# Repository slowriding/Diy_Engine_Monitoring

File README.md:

# Diy_Engine_Monitoring
Read and display Powertrain sensors and control outputs with DIY PCB, code and display.

Project started to facilitate features lost due to swapping in newer engine into older computer controlled vehicle.  
It overlays a secondary set of sensors and a display unit showing gauges.  The controller drives outputs for variable speed loads like fans and fuel pump and switched loads.
Goals are for the system to be as simple as possible, hackable and start immediately without having to boot an operating system.

Current design uses a common Arduino module programmed in C.  This project welcomes submissions of improvements or complete redesigns.
OBDII and GM LAN integration are intended but not completed.

Test article implementation:
2002 Chevrolet Tahoe with original 5.3L, LS3 GEN III, gas engine that failed and Chevrolet Performance E-ROD LS3, LS3 GEN IV, powertrain was installed with 6-speed manual transmission necessitating ECU swap.  The communications network is too different to interconnect directly.  The original dashboard gauges and A/C became completely non-functional due to removed original ECU and features not implemented in newer but generic engine controller.

This project side steps difficulties in attempting to build a protocol converter; for the time being.  Requirements are met by adding a layer of sensors and outputs to replace missing features and adding some extra functionality.  I (original contributor) intend to hack my 2002 Tahoe dash adding pwm driver outputs to drive stock gauge needles.  This will also control new style variable volume A/C compressor based on pressure and temperature sensors. 

Design overview:
Sensors types:  // currently implemented but not all yet working
	Resistive (coolant & oil temp and fuel level).
	0-5V transducers (oil, fuel, evap. and A/C high pressure)
	0-5V ECU outputs (throttle and map)
	Pulse frequency (RPM and vehicle speed)
	Switched (ac & recirculation requests)
	1-wire temperature probes (outside air and A/C condenser temperatures)
 
Outputs types:
	PWM Gauges Drivers (fuel level, oil pressure, coolant temperature, MPH)
	PWM Loads (fan1, fan2, Variable A/C compressor, Fuel Pump speed)

Interface:
	Display - Nextion brand Intelligent LCD display used due to it’s simple serial port/text based connection.  
 	All the graphics are stored and processed on the display. 
	I2c & SPI connections for future ODB2 interfaces.
Programming:
	Currently written in C, with migration to RUST intended for future releases.
	The Tahoe.h file isolates MCU pin definitions, calibrations and variable definitions.

Please consider contributing to this evolving project as much can be improved

Files: 
	Schmatic: See .pdf files in root or Open directorys in KiCAD One is the PCB and the other shows the wiring currenly used on authors Tahoe
 	Code: Open Using Arduino software 
  	PCB design files are newer than revision being tested (PCB photo).  Newer version has better voltage regulation and is physiclly smaller.

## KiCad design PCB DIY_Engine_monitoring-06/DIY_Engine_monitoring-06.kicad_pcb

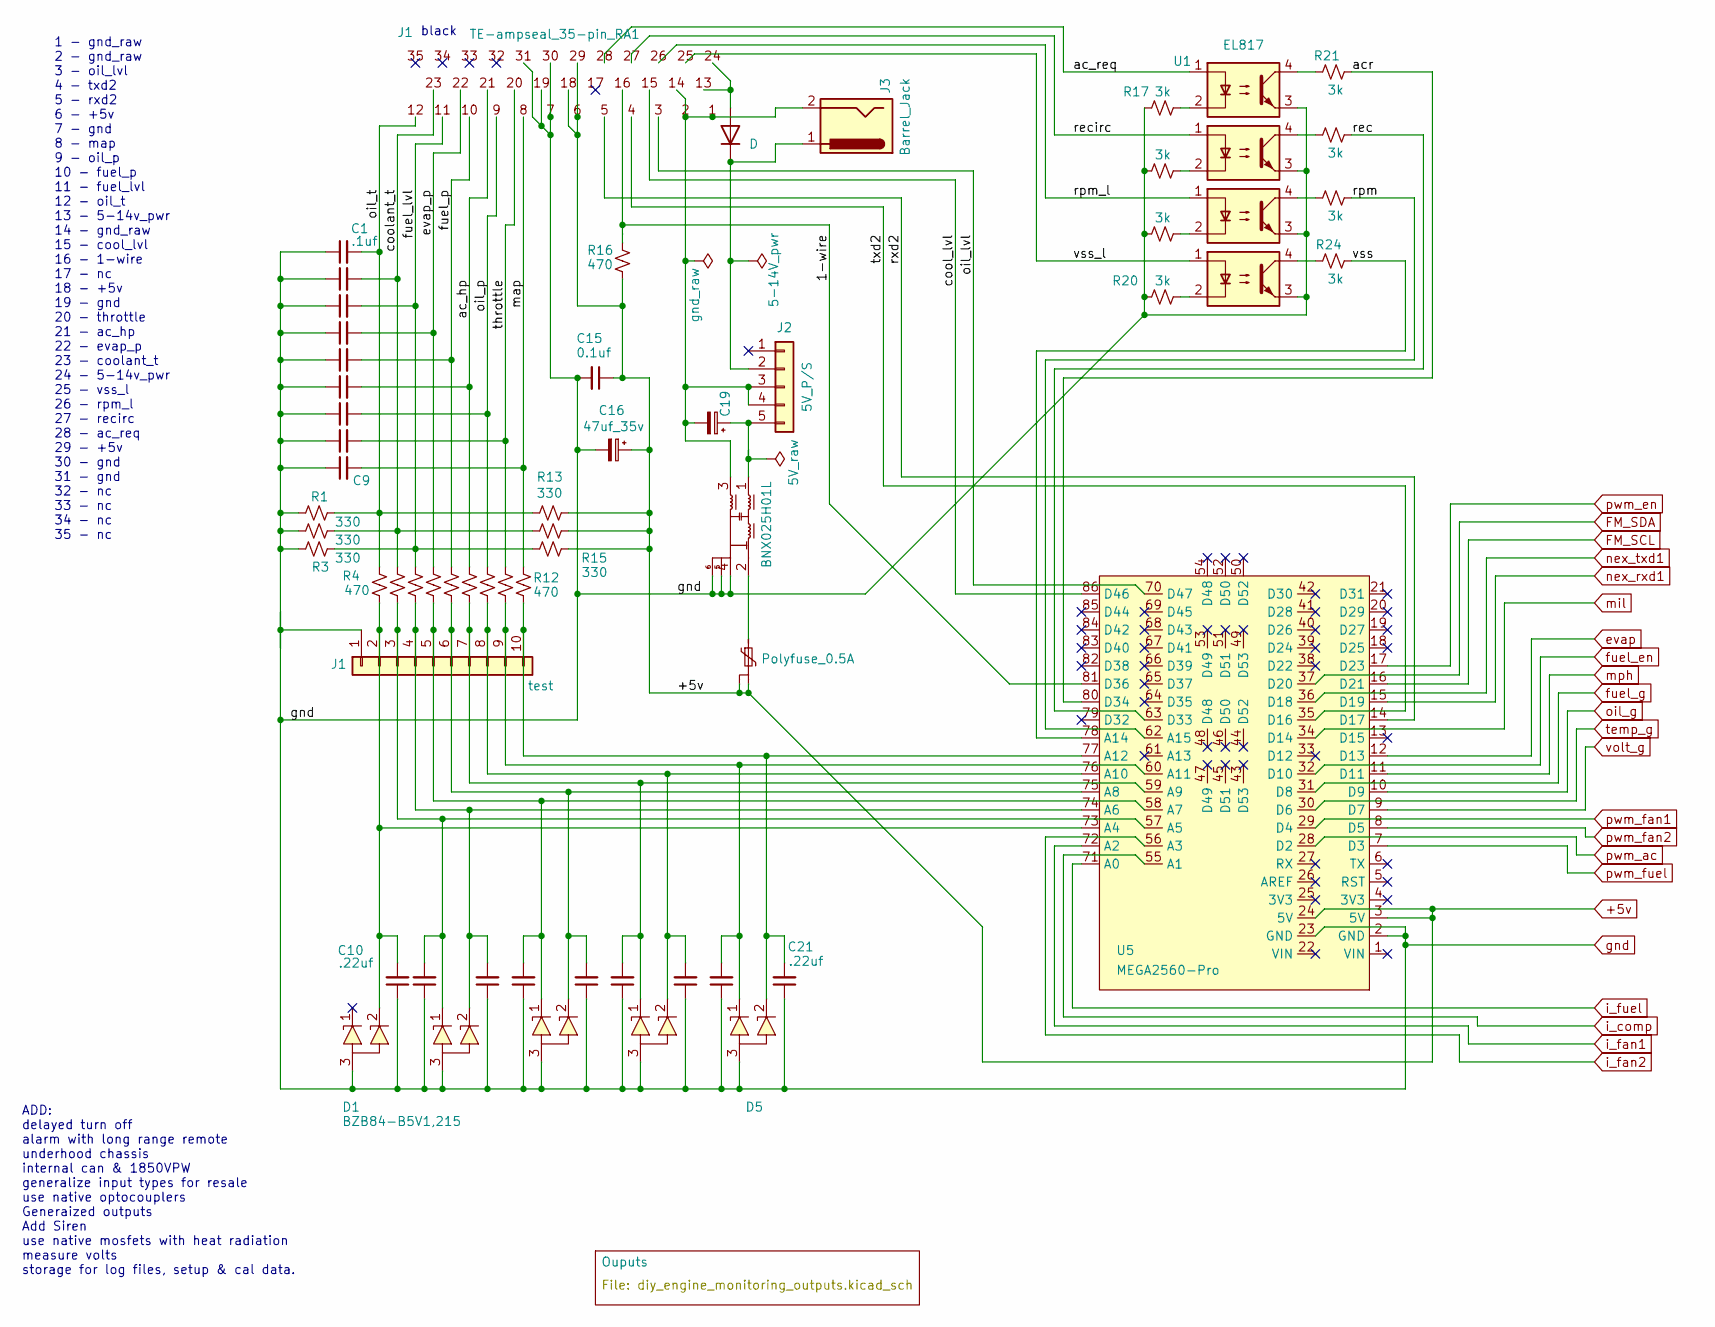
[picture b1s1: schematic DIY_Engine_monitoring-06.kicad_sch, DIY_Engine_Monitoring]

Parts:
C1, C2, C3, C4, C5, C6, C7, C8, C9: .1uf; C_0805_2012Metric
C10, C11, C12, C13, C14, C17, C18, C20, C21: .22uf; C_0805_2012Metric
C15: 0.1uf; C_0805_2012Metric
C16: 47uf_35v; CP_Radial_D6.3mm_P2.50mm
C19: 47uf_50v; CP_Radial_D8.0mm_P5.00mm
D1, D2, D3, D4, D5: BZB84-B5V1,215; SOT-23
D22: D
F1: Polyfuse_0.5A; Littelfuse_PolyZen-LS
FL1: BNX025H01L; Filter_Murata_BNX025_ThermalVias
J1: test; PinHeader_1x10_P2.54mm_Vertical
J2: 5V_P/S; PinSocket_1x05_P2.54mm_Vertical
J3: Barrel_Jack; BarrelJack_Horizontal
R1, R2, R3, R13, R14, R15: 330; R_0805_2012Metric_Pad1.20x1.40mm_HandSolder
R4, R5, R6, R7, R8, R9, R10, R11, R12, R16: 470; R_0805_2012Metric_Pad1.20x1.40mm_HandSolder
R17, R18, R19, R20, R21, R22, R23, R24: 3k; R_0805_2012Metric
TE-ampseal_35-pin_RA1: J1; TE_AMPSEAL_1-776163-x_3Rows_35_P0.4mm_Horizontal
U1, U2, U3, U4: EL817; DIP-4_W7.62mm
U5: MEGA2560-Pro

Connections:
+5v: C15.1, C16.1, F1.2, F1.3, R13.1, R14.1, R15.2, R16.2, TE-ampseal_35-pin_RA1.6, TE-ampseal_35-pin_RA1.18, TE-ampseal_35-pin_RA1.29, U5.3 (5V), U5.24 (5V); also elsewhere on the board
/1-wire: R16.1, TE-ampseal_35-pin_RA1.16, U5.81 (D36)
/ac_hp: C6.2, R9.1, TE-ampseal_35-pin_RA1.21
/ac_req: TE-ampseal_35-pin_RA1.28, U1.1
/acr: R21.2, U5.80 (D34)
/cool_lvl: TE-ampseal_35-pin_RA1.15, U5.86 (D46)
/coolant_t: C2.2, R2.2, R5.2, R14.2, TE-ampseal_35-pin_RA1.23
/evap_p: C4.2, R7.1, TE-ampseal_35-pin_RA1.22
/fuel_lvl: C3.2, R3.2, R6.1, R15.1, TE-ampseal_35-pin_RA1.11
/fuel_p: C5.2, R8.1, TE-ampseal_35-pin_RA1.10
/map: C9.2, R12.1, TE-ampseal_35-pin_RA1.8
/oil_lvl: TE-ampseal_35-pin_RA1.3, U5.70 (D47)
/oil_p: C7.2, R10.1, TE-ampseal_35-pin_RA1.9
/oil_t: C1.2, R1.2, R4.1, R13.2, TE-ampseal_35-pin_RA1.12
/rec: R22.2, U5.63 (D33)
/recirc: TE-ampseal_35-pin_RA1.27, U2.1
/rpm: R23.2, U5.62 (A15)
/rpm_l: TE-ampseal_35-pin_RA1.26, U3.1
/rxd2: TE-ampseal_35-pin_RA1.5, U5.14 (D17)
/throttle: C8.2, R11.1, TE-ampseal_35-pin_RA1.20
/txd2: TE-ampseal_35-pin_RA1.4, U5.35 (D16)
/vss: R24.2, U5.78 (A14)
/vss_l: TE-ampseal_35-pin_RA1.25, U4.1
FM_SCL: U5.16 (D21); also elsewhere on the board
FM_SDA: U5.37 (D20); also elsewhere on the board
unnamed: C10.2, D1.2 (A), J1.2, R4.2, U5.73 (A4)
unnamed: C12.2, D2.2 (A), J1.4, R6.2, U5.74 (A6)
unnamed: C14.2, D3.2 (A), J1.6, R8.2, U5.75 (A8)
unnamed: C18.2, D4.2 (A), J1.8, R10.2, U5.76 (A10)
unnamed: C21.2, D5.2 (A), J1.10, R12.2, U5.77 (A12)
unnamed: F1.1, FL1.2
unnamed: C11.2, D2.1 (K), J1.3, R5.1, U5.57 (A5)
unnamed: C13.2, D3.1 (K), J1.5, R7.2, U5.58 (A7)
unnamed: C17.2, D4.1 (K), J1.7, R9.2, U5.59 (A9)
unnamed: C20.2, D5.1 (K), J1.9, R11.2, U5.60 (A11)
unnamed: C19.2, FL1.3, J2.3, J2.4, J3.2, TE-ampseal_35-pin_RA1.1, TE-ampseal_35-pin_RA1.2, TE-ampseal_35-pin_RA1.14
unnamed: C19.1, FL1.1, J2.5
unnamed: R17.2, U1.2
unnamed: R18.2, U2.2
unnamed: R19.2, U3.2
unnamed: R20.2, U4.2
unnamed: R21.1, U1.4
unnamed: R22.1, U2.4
unnamed: R23.1, U3.4
unnamed: R24.1, U4.4
evap: U5.12 (D13); also elsewhere on the board
fuel_en: U5.32 (D10); also elsewhere on the board
fuel_g: U5.31 (D8); also elsewhere on the board
gnd: C1.1, C2.1, C3.1, C4.1, C5.1, C6.1, C7.1, C8.1, C9.1, C10.1, C11.1, C12.1, C13.1, C14.1, C15.2, C16.2, C17.1, C18.1, C20.1, C21.1, D1.3 (K), D2.3 (K), D3.3 (K), D4.3 (K), D5.3 (K), FL1.4, FL1.5, FL1.6, J1.1, R1.1, R2.1, R3.1, R17.1, R18.1, R19.1, R20.1, TE-ampseal_35-pin_RA1.7, TE-ampseal_35-pin_RA1.19, TE-ampseal_35-pin_RA1.30, TE-ampseal_35-pin_RA1.31, U1.3, U2.3, U3.3, U4.3, U5.2 (GND), U5.23 (GND); also elsewhere on the board
i_comp: U5.55 (A1); also elsewhere on the board
i_fan1: U5.72 (A2); also elsewhere on the board
i_fan2: U5.56 (A3); also elsewhere on the board
i_fuel: U5.71 (A0); also elsewhere on the board
mil: U5.34 (D14); also elsewhere on the board
mph: U5.11 (D11); also elsewhere on the board
nex_rxd1: U5.15 (D19); also elsewhere on the board
nex_txd1: U5.36 (D18); also elsewhere on the board
oil_g: U5.10 (D9); also elsewhere on the board
pwm_ac: U5.28 (D2); also elsewhere on the board
pwm_en: U5.17 (D23); also elsewhere on the board
pwm_fan1: U5.29 (D4); also elsewhere on the board
pwm_fan2: U5.8 (D5); also elsewhere on the board
pwm_fuel: U5.7 (D3); also elsewhere on the board
temp_g: U5.30 (D6); also elsewhere on the board
volt_g: U5.9 (D7); also elsewhere on the board

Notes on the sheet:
ADD: delayed turn off alarm with long range remote underhood chassis internal can & 1850VPW generalize input types for resale use native optocouplers Generaized outputs Add Siren use native mosfets with heat radiation measure volts storage for log files, setup & cal data.
1 - gnd_raw 2 - gnd_raw 3 - oil_lvl 4 - txd2 5 - rxd2 6 - +5v 7 - gnd 8 - map 9 - oil_p 10 - fuel_p 11 - fuel_lvl 12 - oil_t 13 - 5-14v_pwr 14 - gnd_raw 15 - cool_lvl 16 - 1-wire 17 - nc 18 - +5v 19 - gnd 20 - throttle 21 - ac_hp 22 - evap_p 23 - coolant_t 24 - 5-14v_pwr 25 - vss_l 26 - rpm_l 27 - 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
black

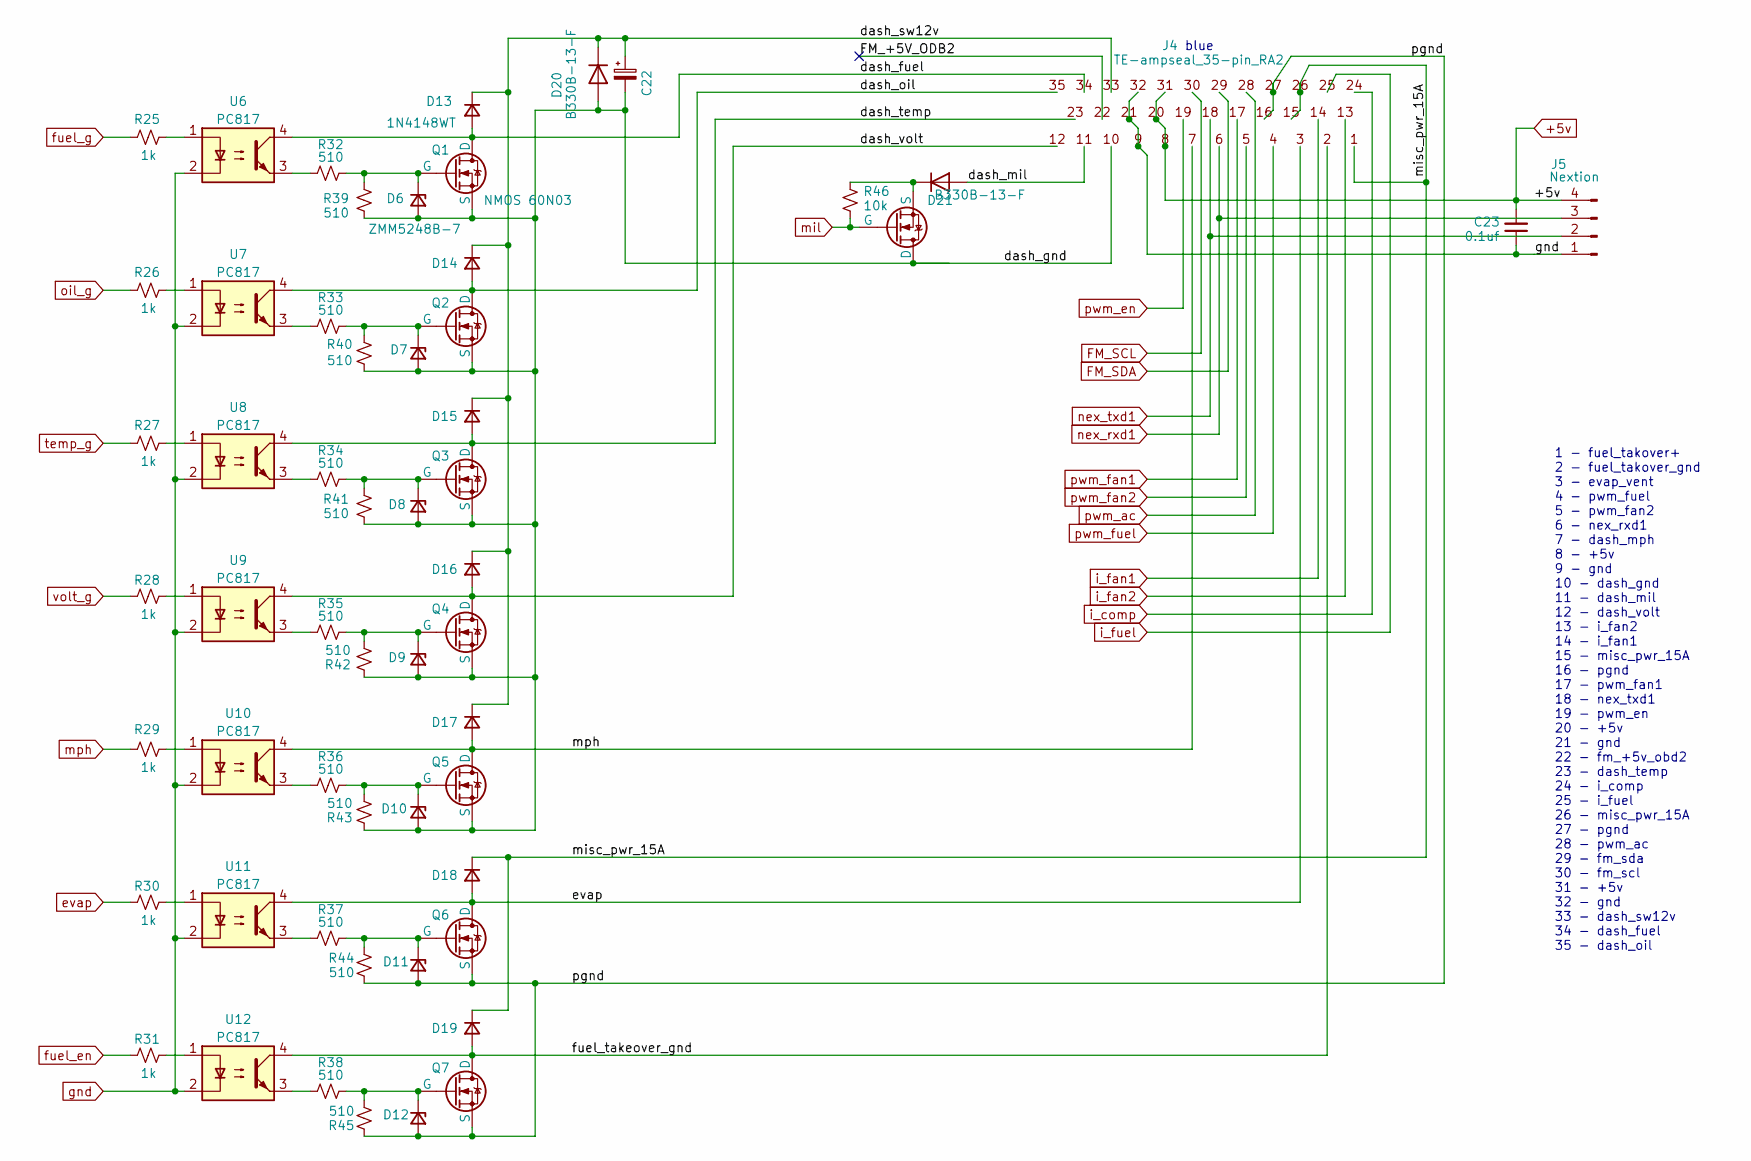
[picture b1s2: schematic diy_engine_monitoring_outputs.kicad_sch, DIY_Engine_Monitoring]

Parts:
C22: C_Polarized_Small; C_Disc_D5.0mm_W2.5mm_P5.00mm
C23: 0.1uf; C_0805_2012Metric
D6, D7, D8, D9, D10, D11, D12: ZMM5248B-7; D_SOD-523
D13, D14, D15, D16, D17, D18, D19: 1N4148WT; D_SOD-323F
D20, D21: B330B-13-F; D_SMB
J4: TE-ampseal_35-pin_RA2; TE_AMPSEAL_1-776163-x_3Rows_35_P0.4mm_Horizontal
J5: Nextion; JST_EH_B4B-EH-A_1x04_P2.50mm_Vertical
Q1, Q2, Q3, Q4, Q5, Q6, Q7: NMOS 60N03; TO-252-3_TabPin2
Q8: NMOS; TO-220F-3_Horizontal_TabDown
R25, R26, R27, R28, R29, R30, R31: 1k; R_0805_2012Metric_Pad1.20x1.40mm_HandSolder
R32, R33, R34, R35, R36, R37, R38, R39, R40, R41, R42, R43, R44, R45: 510; R_0805_2012Metric_Pad1.20x1.40mm_HandSolder
R46: 10k; R_0805_2012Metric
U6, U7, U8, U9, U10, U11, U12: PC817; DIP-4_W7.62mm

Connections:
+5v: C23.2, J4.8, J4.20, J4.31, J5.4; also elsewhere on the board
/Ouputs/FM_+5V_ODB2: J4.22
/Ouputs/dash_fuel: D13.2 (A), J4.34, Q1.1 (D), U6.4
/Ouputs/dash_gnd: C22.2, D6.2 (A), D7.2 (A), D8.2 (A), D9.2 (A), D10.2 (A), D20.2 (A), J4.10, Q1.3 (S), Q2.3 (S), Q3.3 (S), Q4.3 (S), Q5.3 (S), Q8.1 (D), R39.1, R40.1, R41.1, R42.1, R43.1
/Ouputs/dash_mil: D21.2 (A), J4.11
/Ouputs/dash_oil: D14.2 (A), J4.35, Q2.1 (D), U7.4
/Ouputs/dash_sw12v: C22.1, D13.1 (K), D14.1 (K), D15.1 (K), D16.1 (K), D17.1 (K), D20.1 (K), J4.33
/Ouputs/dash_temp: D15.2 (A), J4.23, Q3.1 (D), U8.4
/Ouputs/dash_volt: D16.2 (A), J4.12, Q4.1 (D), U9.4
/Ouputs/fuel_takeover_gnd: D19.2 (A), J4.2, Q7.1 (D), U12.4
/Ouputs/misc_pwr_15A: D18.1 (K), D19.1 (K), J4.1, J4.15, J4.26
/Ouputs/pgnd: D11.2 (A), D12.2 (A), J4.16, J4.27, Q6.3 (S), Q7.3 (S), R44.1, R45.1
FM_SCL: J4.30; also elsewhere on the board
FM_SDA: J4.29; also elsewhere on the board
unnamed: D6.1 (K), Q1.2 (G), R32.2, R39.2
unnamed: D7.1 (K), Q2.2 (G), R33.2, R40.2
unnamed: D8.1 (K), Q3.2 (G), R34.2, R41.2
unnamed: D9.1 (K), Q4.2 (G), R35.2, R42.2
unnamed: D10.1 (K), Q5.2 (G), R36.2, R43.2
unnamed: D11.1 (K), Q6.2 (G), R37.2, R44.2
unnamed: D12.1 (K), Q7.2 (G), R38.2, R45.2
unnamed: D17.2 (A), J4.7, Q5.1 (D), U10.4
unnamed: D18.2 (A), J4.3, Q6.1 (D), U11.4
unnamed: D21.1 (K), Q8.3 (S), R46.1
unnamed: R25.2, U6.1
unnamed: R26.2, U7.1
unnamed: R27.2, U8.1
unnamed: R28.2, U9.1
unnamed: R29.2, U10.1
unnamed: R30.2, U11.1
unnamed: R31.2, U12.1
unnamed: R32.1, U6.3
unnamed: R33.1, U7.3
unnamed: R34.1, U8.3
unnamed: R35.1, U9.3
unnamed: R36.1, U10.3
unnamed: R37.1, U11.3
unnamed: R38.1, U12.3
evap: R30.1; also elsewhere on the board
fuel_en: R31.1; also elsewhere on the board
fuel_g: R25.1; also elsewhere on the board
gnd: C23.1, J4.9, J4.21, J4.32, J5.1, U6.2, U7.2, U8.2, U9.2, U10.2, U11.2, U12.2; also elsewhere on the board
i_comp: J4.24; also elsewhere on the board
i_fan1: J4.14; also elsewhere on the board
i_fan2: J4.13; also elsewhere on the board
i_fuel: J4.25; also elsewhere on the board
mil: Q8.2 (G), R46.2; also elsewhere on the board
mph: R29.1; also elsewhere on the board
nex_rxd1: J4.6, J5.3; also elsewhere on the board
nex_txd1: J4.18, J5.2; also elsewhere on the board
oil_g: R26.1; also elsewhere on the board
pwm_ac: J4.28; also elsewhere on the board
pwm_en: J4.19; also elsewhere on the board
pwm_fan1: J4.17; also elsewhere on the board
pwm_fan2: J4.5; also elsewhere on the board
pwm_fuel: J4.4; also elsewhere on the board
temp_g: R27.1; also elsewhere on the board
volt_g: R28.1; also elsewhere on the board

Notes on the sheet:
1 - fuel_takover+ 2 - fuel_takover_gnd 3 - evap_vent 4 - pwm_fuel 5 - pwm_fan2 6 - nex_rxd1 7 - dash_mph 8 - +5v 9 - gnd 10 - dash_gnd 11 - dash_mil 12 - dash_volt 13 - i_fan2 14 - i_fan1 15 - misc_pwr_15A 16 - pgnd 17 - pwm_fan1 18 - nex_txd1 19 - pwm_en 20 - +5v 21 - gnd 22 - fm_+5v_obd2 23 - das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
blue

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
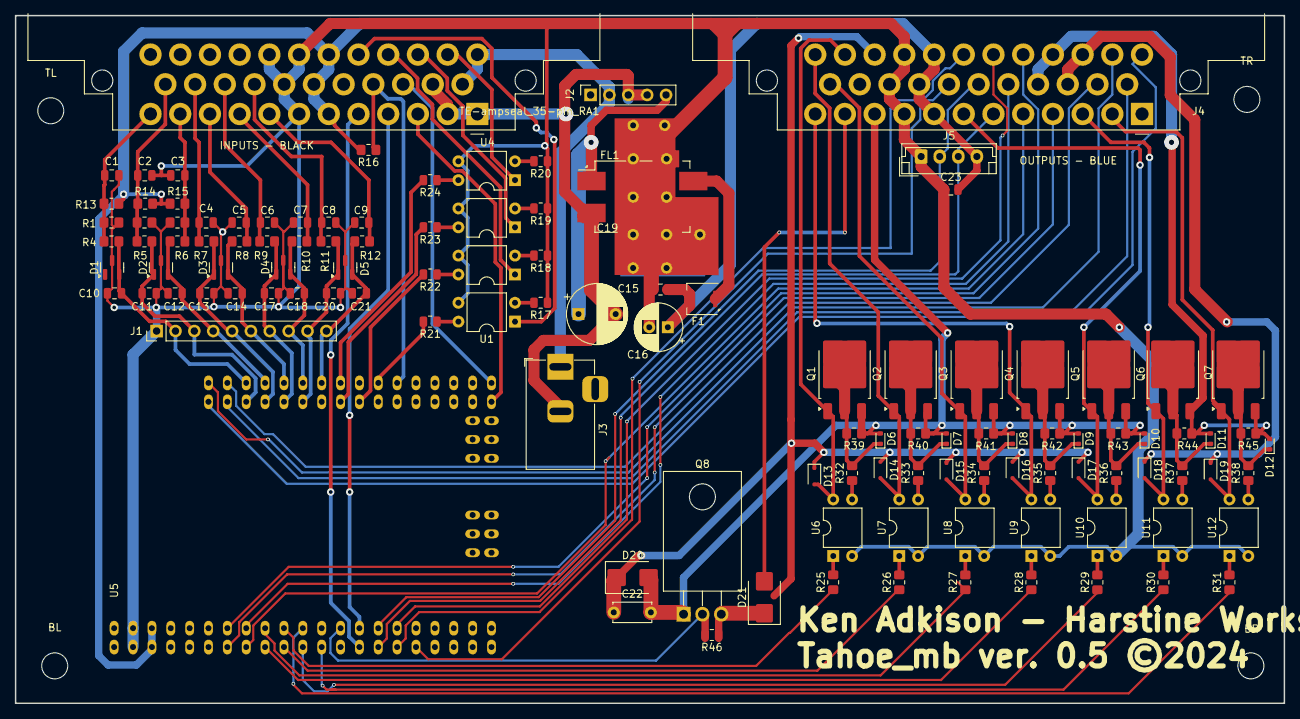
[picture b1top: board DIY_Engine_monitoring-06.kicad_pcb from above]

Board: 2 copper layers, 170.8 x 92.6 mm, 122 parts (0 on the bottom side), 100 nets.

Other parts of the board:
BL: MountingHole_3.5mm
BR: MountingHole_3.5mm
TL: MountingHole_3.5mm
TR: MountingHole_3.5mm

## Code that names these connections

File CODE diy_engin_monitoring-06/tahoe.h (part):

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uint16_t evap_press;

// ANALOG INPUTS              // Nextion fields
const int i_fuel       = A0;  // n73
const int i_comp       = A1;  // n72
const int i_fan1       = A2;  // n70
const int i_fan2       = A3;  // n71
const int oil_t_pin    = A4;  // n5:x5
const int cool_t_pin   = A5;  // n3:x3
const int fuel_l_pin   = A6;  // n4:x4
const int evap_pin     = A7;  // n7:x7
const int fuel_p_pin   = A8;  // n6:x6
const int ac_hp_pin    = A9;   // n10:x10
const int oil_p_pin    = A10;  // n2:x2
const int thr_pin      = A11;  // n8:x8
const int map_pin      = A12;  // n9:x9
const int vss_pin      = A14;  // n0:raw x0:mph
const int rpm_pin      = A15;  // n1:raw x1:rpm

const int ad_pins[] = {A0, A1, A2, A3, A4, A5, A6, A7, A8, A9, A10, A11, A12, A13, A14, A15};

// DIGITAL INPUTS
const int ac_req_pin   = 34;
const int ac_recirc_pin= 33;
const int oil_lvl_pin  = 28;
const int cool_lvl_pin = 32;

// const int one_wire_pin = A13;

// OUTPUTS
const int pwm_ac_pin   = 2;
const int pwm_fuel_pin = 3;
const int fan1_pin     = 4;
const int fan2_pin     = 5;

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const int voltg_pin    = 7;
const int fuelg_pin    = 8;
const int oilg_pin     = 9;
const int fuel_en_pin  = 10;
const int mphg_pin     = 11;
const int evap_sol_pin = 13;  
const int mil_pin      = 14;
const int pwm_en_pin   = 23;

// Global variables
// static char buff[100]; // for CAN msgs via wire  //  ??? not used
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bool evap     = false;


uint8_t rpm_l    = 0;
uint8_t mph_l    = 0;
uint8_t fan1     = 0;
uint8_t fan2     = 0;
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#define ac_dis_tps 90
#define ac_en_tps  30

#define I_FUEL 0   // Index to arrays
#define I_COMP 1
#define I_FAN1 2
#define I_FAN2 3

#define OIL_T  4
#define COOL_T 5
#define FUEL_L 6

#define EVAP   7
#define FUEL_P 8
#define AC_HP  9
#define OIL_P  10
#define THR    11
#define MAP    12


struct calVal {
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
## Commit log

2024-12-14 Update README.md
    Original post
2024-12-14 Initial post of Schematic and Code to Git
2024-12-19 Updates include photos, harness drawings and code
    Early prototype partally working. Photos of Earlier version undergoing testing. PCB files are for next version.
2024-12-21 Many calibrations made
    Still early days of getting code fixes and analog inputs calibrated
2024-12-29 Initial testing in driven vehicle

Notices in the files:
PCB DIY_Engine_monitoring-06/DIY_Engine_monitoring-06.kicad_pcb:
Tahoe_mb ver. 0.5 ©2024
